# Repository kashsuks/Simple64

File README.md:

# Simple64
A simple 64 key keyboard that warps inwards

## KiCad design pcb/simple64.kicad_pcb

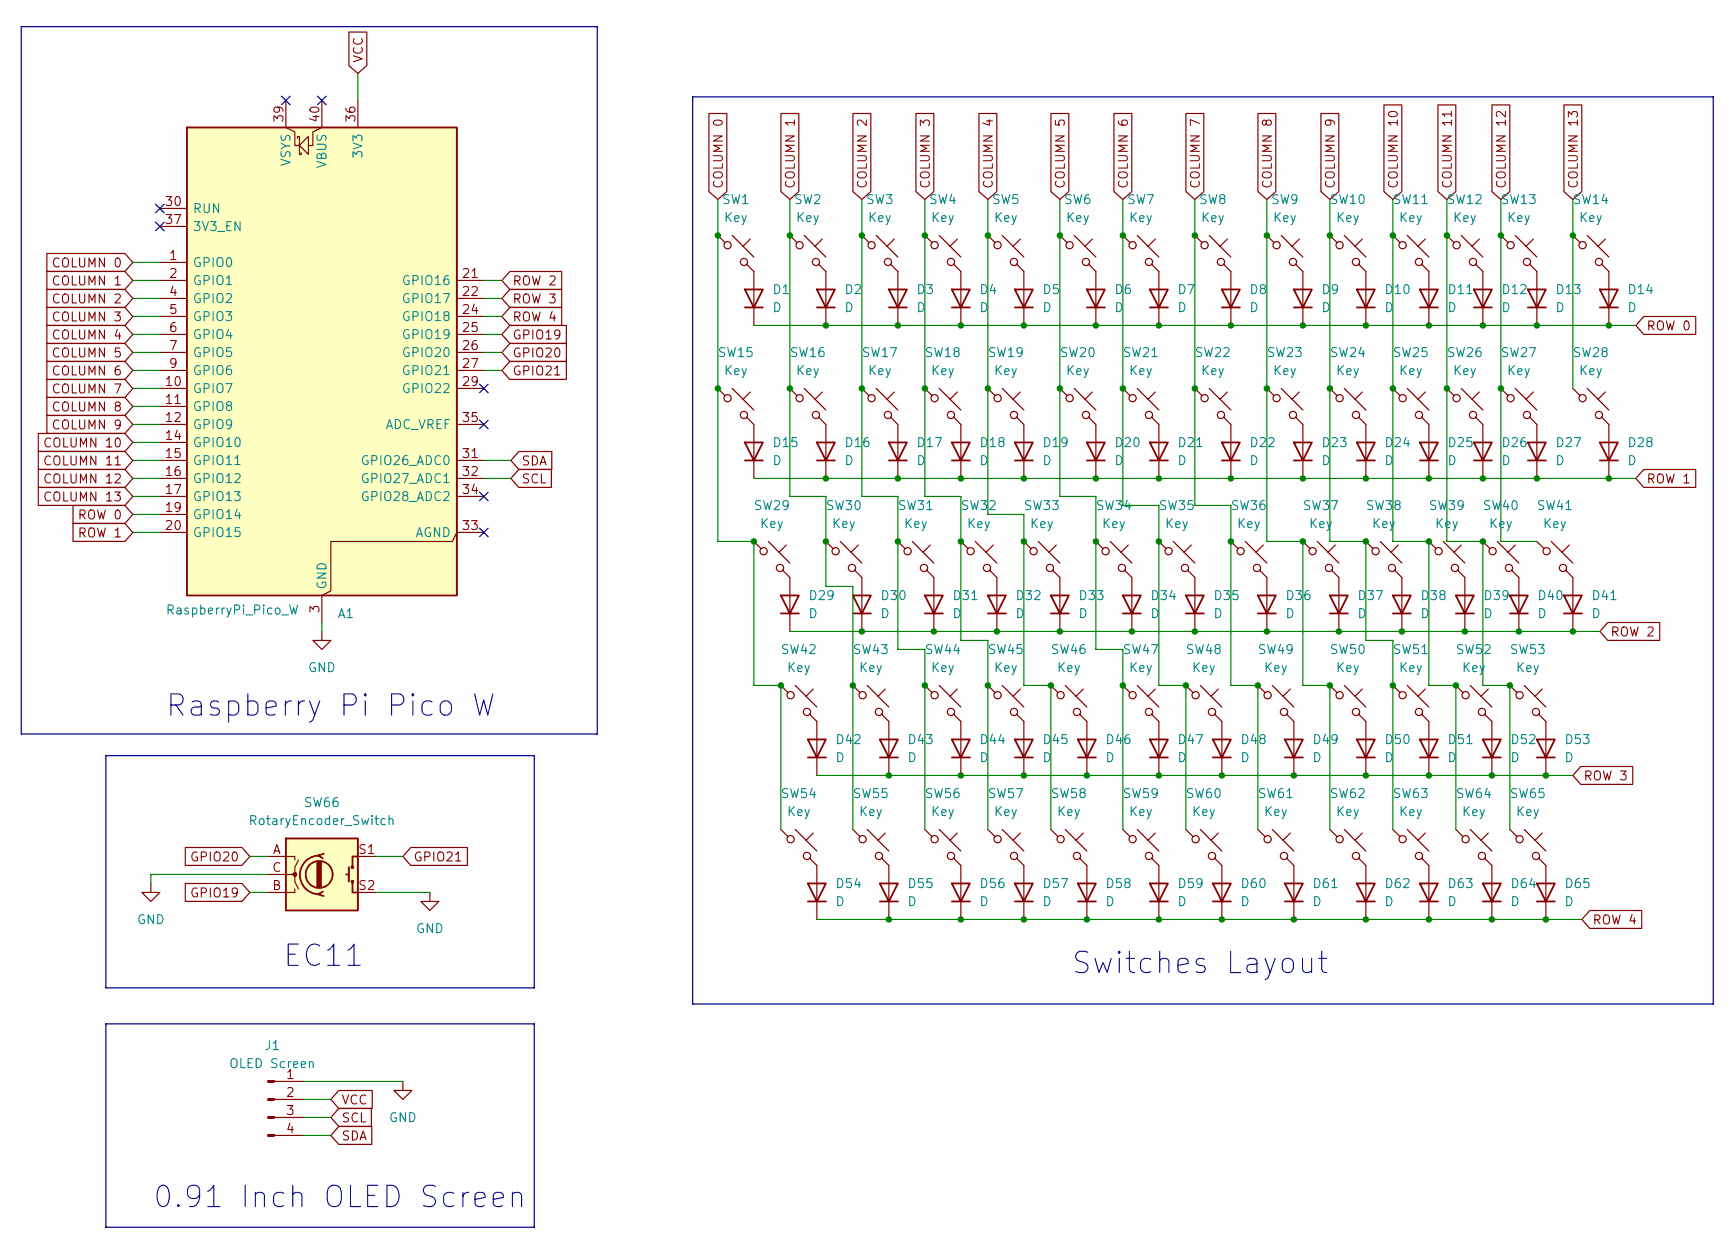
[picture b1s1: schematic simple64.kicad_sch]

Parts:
A1: RaspberryPi_Pico_W; MODULE_SC0918
D1, D2, D3, D4, D5, D6, D7, D8, D9, D10, D11, D12, D13, D14, D15, D16, D17, D18, D19, D20, D21, D22, D23, D24, D25, D26, D27, D28, D29, D30, D31, D32, D33, D34, D35, D36, D37, D38, D39, D40, D41, D42, D43, D44, D45, D46, D47, D48, D49, D50, D51, D52, D53, D54, D55, D56, D57, D58, D59, D60, D61, D62, D63, D64, D65: D; Diode_DO-35
J1: OLED Screen; OLED_128x32
SW1, SW2, SW3, SW4, SW5, SW6, SW7, SW8, SW9, SW10, SW11, SW12, SW13, SW14, SW15, SW16, SW17, SW18, SW19, SW20, SW21, SW22, SW23, SW24, SW25, SW26, SW27, SW28, SW29, SW30, SW31, SW32, SW33, SW34, SW35, SW36, SW37, SW38, SW39, SW40, SW41, SW42, SW43, SW44, SW45, SW46, SW47, SW48, SW49, SW50, SW51, SW52, SW53, SW54, SW55, SW56, SW57, SW58, SW59, SW60, SW61, SW62, SW63, SW64, SW65: Key; SW_Cherry_MX_1.00u_PCB
SW66: RotaryEncoder_Switch; RotaryEncoder_Alps_EC11E-Switch_Vertical_H20mm_CircularMoun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

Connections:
COLUMN 0: A1.1 (GPIO0), SW1.1, SW15.1, SW29.1, SW42.1, SW54.1
COLUMN 1: A1.2 (GPIO1), SW2.1, SW16.1, SW30.1, SW43.1, SW55.1
COLUMN 2: A1.4 (GPIO2), SW3.1, SW17.1, SW31.1, SW44.1, SW56.1
COLUMN 3: A1.5 (GPIO3), SW4.1, SW18.1, SW32.1, SW45.1, SW57.1
COLUMN 4: A1.6 (GPIO4), SW5.1, SW19.1, SW33.1, SW46.1, SW58.1
COLUMN 5: A1.7 (GPIO5), SW6.1, SW20.1, SW34.1, SW47.1, SW59.1
COLUMN 6: A1.9 (GPIO6), SW7.1, SW21.1, SW35.1, SW48.1, SW60.1
COLUMN 7: A1.10 (GPIO7), SW8.1, SW22.1, SW36.1, SW49.1, SW61.1
COLUMN 8: A1.11 (GPIO8), SW9.1, SW23.1, SW37.1, SW50.1, SW62.1
COLUMN 9: A1.12 (GPIO9), SW10.1, SW24.1, SW38.1, SW51.1, SW63.1
COLUMN 10: A1.14 (GPIO10), SW11.1, SW25.1, SW39.1, SW52.1, SW64.1
COLUMN 11: A1.15 (GPIO11), SW12.1, SW26.1, SW40.1, SW53.1, SW65.1
COLUMN 12: A1.16 (GPIO12), SW13.1, SW27.1, SW41.1
COLUMN 13: A1.17 (GPIO13), SW14.1, SW28.1
GND: A1.3 (GND), A1.8 (GND), A1.13 (GND), A1.18 (GND), A1.23 (GND), A1.28 (GND), A1.38 (GND), J1.1, SW66.C, SW66.S2
GPIO19: A1.25 (GPIO19), SW66.B
GPIO20: A1.26 (GPIO20), SW66.A
GPIO21: A1.27 (GPIO21), SW66.S1
unnamed: D1.2 (A), SW1.2
unnamed: D2.2 (A), SW2.2
unnamed: D3.2 (A), SW3.2
unnamed: D4.2 (A), SW4.2
unnamed: D5.2 (A), SW5.2
unnamed: D6.2 (A), SW6.2
unnamed: D7.2 (A), SW7.2
unnamed: D8.2 (A), SW8.2
unnamed: D9.2 (A), SW9.2
unnamed: D10.2 (A), SW10.2
unnamed: D11.2 (A), SW11.2
unnamed: D12.2 (A), SW12.2
unnamed: D13.2 (A), SW13.2
unnamed: D14.2 (A), SW14.2
unnamed: D15.2 (A), SW15.2
unnamed: D16.2 (A), SW16.2
unnamed: D17.2 (A), SW17.2
unnamed: D18.2 (A), SW18.2
unnamed: D19.2 (A), SW19.2
unnamed: D20.2 (A), SW20.2
unnamed: D21.2 (A), SW21.2
unnamed: D22.2 (A), SW22.2
unnamed: D23.2 (A), SW23.2
unnamed: D24.2 (A), SW24.2
unnamed: D25.2 (A), SW25.2
unnamed: D26.2 (A), SW26.2
unnamed: D27.2 (A), SW27.2
unnamed: D28.2 (A), SW28.2
unnamed: D29.2 (A), SW29.2
unnamed: D30.2 (A), SW30.2
unnamed: D31.2 (A), SW31.2
unnamed: D32.2 (A), SW32.2
unnamed: D33.2 (A), SW33.2
unnamed: D34.2 (A), SW34.2
unnamed: D35.2 (A), SW35.2
unnamed: D36.2 (A), SW36.2
unnamed: D37.2 (A), SW37.2
unnamed: D38.2 (A), SW38.2
unnamed: D39.2 (A), SW39.2
unnamed: D40.2 (A), SW40.2
unnamed: D41.2 (A), SW41.2
unnamed: D42.2 (A), SW42.2
unnamed: D43.2 (A), SW43.2
unnamed: D44.2 (A), SW44.2
unnamed: D45.2 (A), SW45.2
unnamed: D46.2 (A), SW46.2
unnamed: D47.2 (A), SW47.2
unnamed: D48.2 (A), SW48.2
unnamed: D49.2 (A), SW49.2
unnamed: D50.2 (A), SW50.2
unnamed: D51.2 (A), SW51.2
unnamed: D52.2 (A), SW52.2
unnamed: D53.2 (A), SW53.2
unnamed: D54.2 (A), SW54.2
unnamed: D55.2 (A), SW55.2
unnamed: D56.2 (A), SW56.2
unnamed: D57.2 (A), SW57.2
unnamed: D58.2 (A), SW58.2
unnamed: D59.2 (A), SW59.2
unnamed: D60.2 (A), SW60.2
unnamed: D61.2 (A), SW61.2
unnamed: D62.2 (A), SW62.2
unnamed: D63.2 (A), SW63.2
unnamed: D64.2 (A), SW64.2
unnamed: D65.2 (A), SW65.2
ROW 0: A1.19 (GPIO14), D1.1 (K), D2.1 (K), D3.1 (K), D4.1 (K), D5.1 (K), D6.1 (K), D7.1 (K), D8.1 (K), D9.1 (K), D10.1 (K), D11.1 (K), D12.1 (K), D13.1 (K), D14.1 (K)
ROW 1: A1.20 (GPIO15), D15.1 (K), D16.1 (K), D17.1 (K), D18.1 (K), D19.1 (K), D20.1 (K), D21.1 (K), D22.1 (K), D23.1 (K), D24.1 (K), D25.1 (K), D26.1 (K), D27.1 (K), D28.1 (K)
ROW 2: A1.21 (GPIO16), D29.1 (K), D30.1 (K), D31.1 (K), D32.1 (K), D33.1 (K), D34.1 (K), D35.1 (K), D36.1 (K), D37.1 (K), D38.1 (K), D39.1 (K), D40.1 (K), D41.1 (K)
ROW 3: A1.22 (GPIO17), D42.1 (K), D43.1 (K), D44.1 (K), D45.1 (K), D46.1 (K), D47.1 (K), D48.1 (K), D49.1 (K), D50.1 (K), D51.1 (K), D52.1 (K), D53.1 (K)
ROW 4: A1.24 (GPIO18), D54.1 (K), D55.1 (K), D56.1 (K), D57.1 (K), D58.1 (K), D59.1 (K), D60.1 (K), D61.1 (K), D62.1 (K), D63.1 (K), D64.1 (K), D65.1 (K)
SCL: A1.32 (GPIO27_ADC1), J1.3
SDA: A1.31 (GPIO26_ADC0), J1.4
VCC: A1.36 (3V3), J1.2

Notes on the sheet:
0.91 Inch OLED Screen
Raspberry Pi Pico W
EC11
Switches Layout

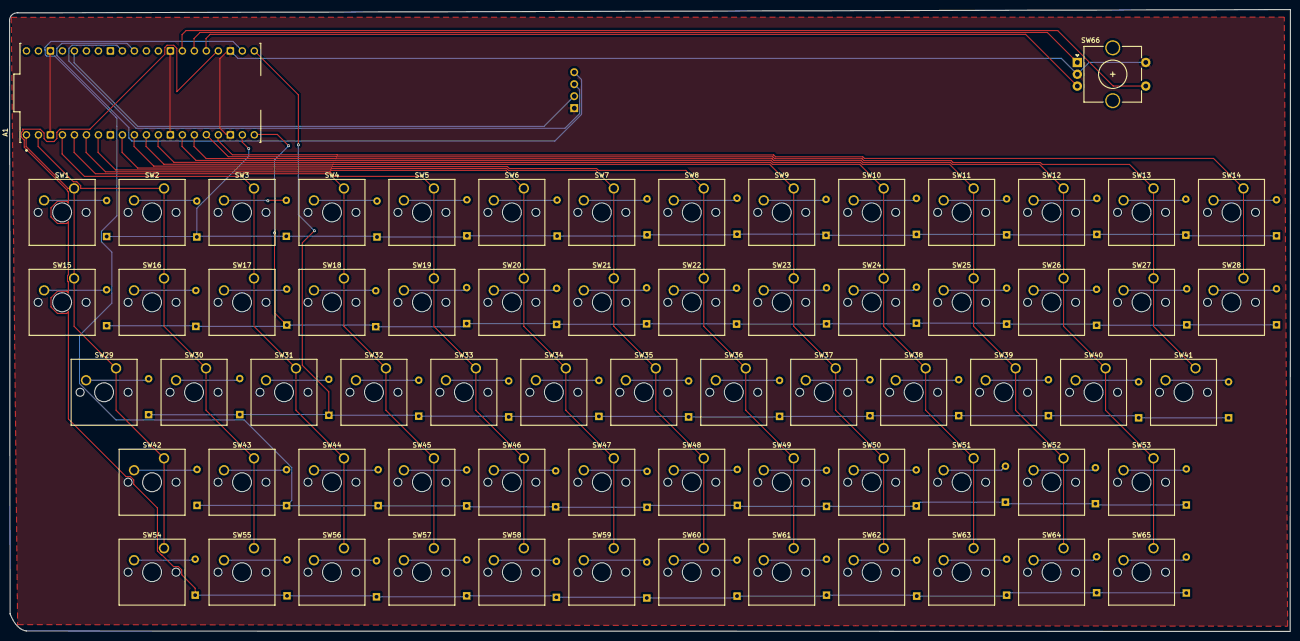
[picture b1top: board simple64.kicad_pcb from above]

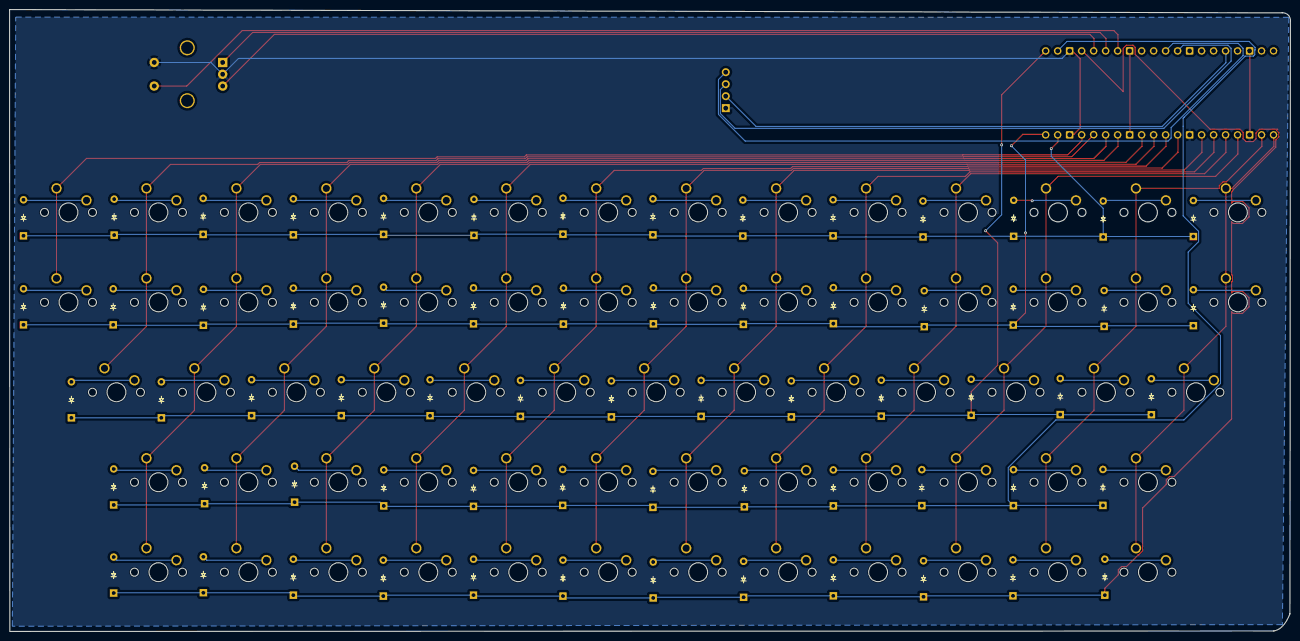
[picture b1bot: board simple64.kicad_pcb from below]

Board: 2 copper layers, 271.3 x 131.7 mm, 133 parts (65 on the bottom side), 91 nets.

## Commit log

2025-08-06 added the schematic stuff
2025-08-08 added the pcb, need to add mounting holes
